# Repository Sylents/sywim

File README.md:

# sywim
sylents wim

Wireless Module for Sylents3 Product
Hardware and Software/Firmware components

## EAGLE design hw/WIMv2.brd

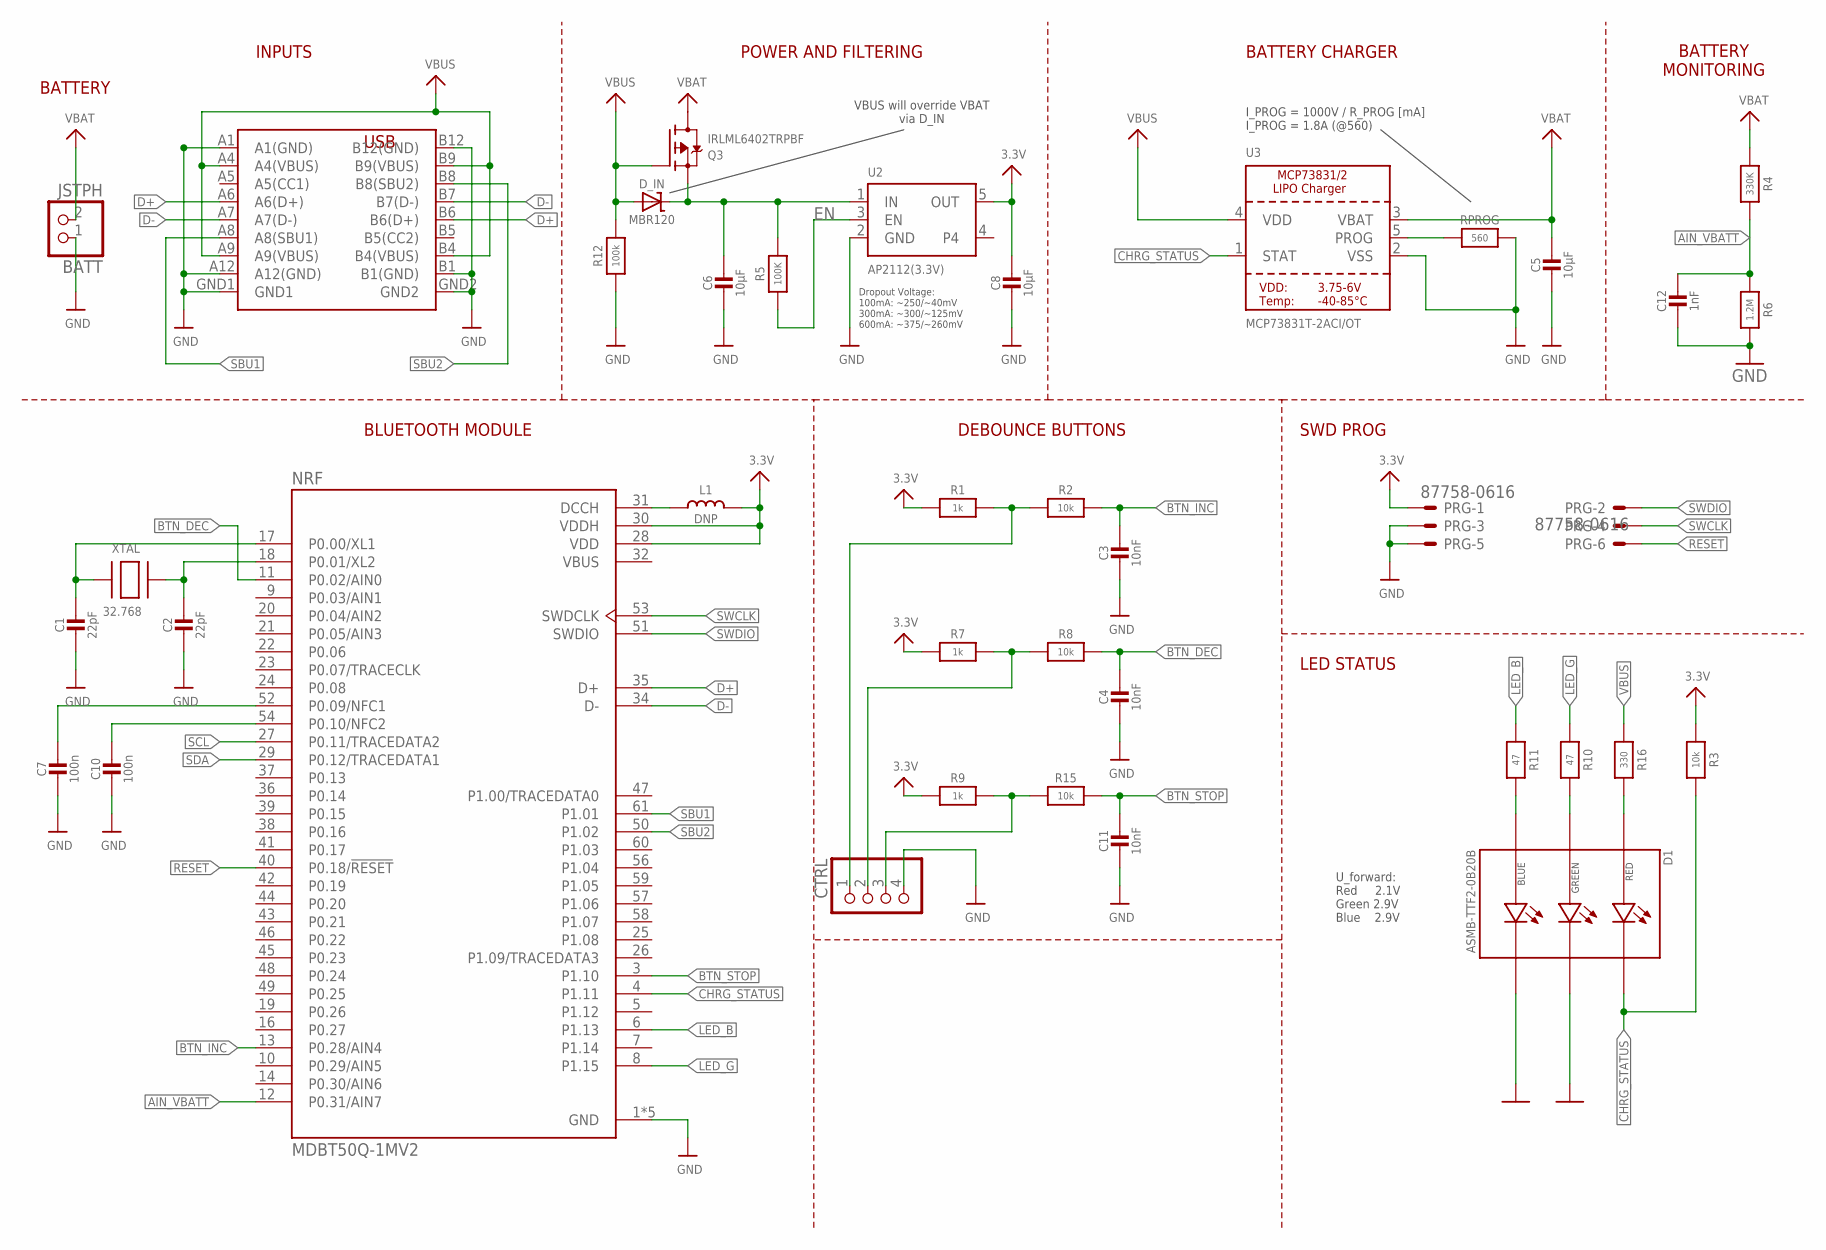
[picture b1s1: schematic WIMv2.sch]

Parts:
BATT: JSTPH; JSTPH2
C1, C2: 22pF; 0603-NO
C3, C4, C11: 10nF; 0603-NO
C5, C6, C8: 10µF; 0805-NO
C7, C10: 100n; 0603-NO
C12: 1nF; 0603-NO
CTRL: PINHD-1X4/90; 1X04/90
D1: ASMB-TTF2-0B20B; LED_ASMB-TTF2-0B20B
D_IN: MBR120; SOD-123
L1: DNP; _0805MP
NRF: MDBT50Q-1MV2; XCVR_MDBT50Q-1MV2
PRG: 87758-0616
Q3: IRLML6402TRPBF; SOT23-R
R1, R7, R9: 1k; 0603-NO
R2, R3, R8, R15: 10k; 0603-NO
R4: 330K; 0603-NO
R5: 100K; 0603-NO
R6: 1.2M; 0603-NO
R10, R11: 47; 0603-NO
R12: 100k; 0603-NO
R16: 330; 0603-NO
RPROG: 560; 0603-NO
U2: AP2112(3.3V); SOT23-5
U3: MCP73831T-2ACI/OT; SOT23-5
USB-C: USB-C; 203615-0003
XTAL: 32.768; XTAL3215

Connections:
3.3V: C8.1, L1.2, NRF.28 (VDD), NRF.30 (VDDH), PRG.1, R1.1, R3.1, R7.1, R9.1, U2.5 (OUT)
AIN_VBATT: C12.1, NRF.12 (P0.31/AIN7), R4.2, R6.1
BTN_DEC: C4.1, NRF.11 (P0.02/AIN0), R8.2
BTN_INC: C3.1, NRF.13 (P0.28/AIN4), R2.2
BTN_STOP: C11.1, NRF.3 (P1.10), R15.2
CHRG_STATUS: D1.2 (R_C), NRF.4 (P1.11), R3.2, U3.1 (STAT)
D+: NRF.35 (D+), USB-C.A6 (A6(D+)), USB-C.B6 (B6(D+))
D-: NRF.34 (D-), USB-C.A7 (A7(D-)), USB-C.B7 (B7(D-))
DCCH: L1.1, NRF.31 (DCCH)
EN: R5.1, U2.3 (EN)
GND: BATT.1, C1.2, C2.2, C3.2, C4.2, C5.2, C6.2, C7.2, C8.2, C10.2, C11.2, C12.2, CTRL.4, D1.4 (G_C), D1.6 (B_C), NRF.1 (GND), NRF.2 (GND), NRF.15 (GND), NRF.33 (GND), NRF.55 (GND), PRG.3, PRG.5, R6.2, R12.1, RPROG.2, U2.2 (GND), U3.2 (VSS), USB-C.A1 (A1(GND)), USB-C.A12 (A12(GND)), USB-C.B1 (B1(GND)), USB-C.B12 (B12(GND)), USB-C.GND1, USB-C.GND2
LED_B: NRF.6 (P1.13), R11.1
LED_G: NRF.8 (P1.15), R10.1
unnamed: C1.1, NRF.17 (P0.00/XL1), XTAL.P$1
unnamed: C2.1, NRF.18 (P0.01/XL2), XTAL.P$2
unnamed: CTRL.1, R1.2, R2.1
unnamed: CTRL.3, R9.2, R15.1
unnamed: CTRL.2, R7.2, R8.1
unnamed: D1.3 (G_A), R10.2
unnamed: D1.5 (B_A), R11.2
unnamed: RPROG.1, U3.5 (PROG)
unnamed: D1.1 (R_A), R16.2
unnamed: C7.1, NRF.52 (P0.09/NFC1)
unnamed: C10.1, NRF.54 (P0.10/NFC2)
RESET: NRF.40 (P0.18/!RESET), PRG.6
SBU1: NRF.61 (P1.01), USB-C.A8 (A8(SBU1))
SBU2: NRF.50 (P1.02), USB-C.B8 (B8(SBU2))
SCL: NRF.27 (P0.11/TRACEDATA2)
SDA: NRF.29 (P0.12/TRACEDATA1)
SWCLK: NRF.53 (SWDCLK), PRG.4
SWDIO: NRF.51 (SWDIO), PRG.2
VBAT: BATT.2, C5.1, Q3.3 (D), R4.1, U3.3 (VBAT)
VBUS: D_IN.A, NRF.32 (VBUS), Q3.1 (G), R12.2, R16.1, U3.4 (VDD), USB-C.A4 (A4(VBUS)), USB-C.A9 (A9(VBUS)), USB-C.B4 (B4(VBUS)), USB-C.B9 (B9(VBUS))
VIN: C6.1, D_IN.C, Q3.2 (S), R5.2, U2.1 (IN)

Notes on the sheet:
I_PROG = 1000V / R_PROG [mA] I_PROG = 1.8A (@560)
BATTERY CHARGER
BATTERY MONITORING
POWER AND FILTERING
INPUTS
VBUS will override VBAT via D_IN
Dropout Voltage: 100mA: ~250/~40mV 300mA: ~300/~125mV 600mA: ~375/~260mV
USB
DEBOUNCE BUTTONS
SWD PROG
BLUETOOTH MODULE
BATTERY
LED STATUS
U_forward: Red 2.1V Green 2.9V Blue 2.9V

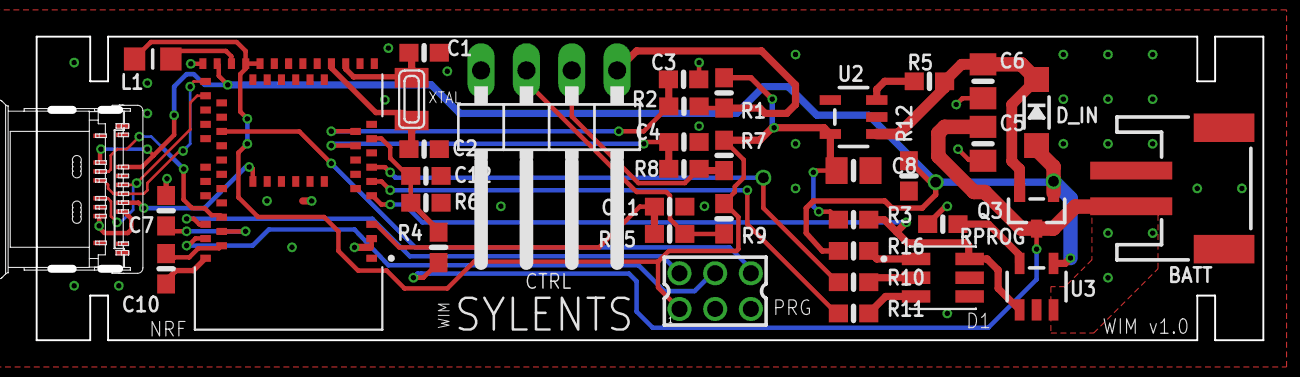
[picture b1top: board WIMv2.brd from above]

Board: 2 copper layers, 68.4 x 16.7 mm, 38 parts (0 on the bottom side), 32 nets.

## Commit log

2023-07-20 add hw
2023-07-20 add fw
2023-07-20 cmu s compileable sources
2023-07-21 changed dir

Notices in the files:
parts and their libraries:
microbuilder: This work is placed in the public domain, and may be freely used for commercial and non-commercial work with the following conditions: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
SparkFun-Aesthetics: Licensing: Creative Commons ShareAlike 4.0 International - https://creativecommons.org/licenses/by-sa/4.0
